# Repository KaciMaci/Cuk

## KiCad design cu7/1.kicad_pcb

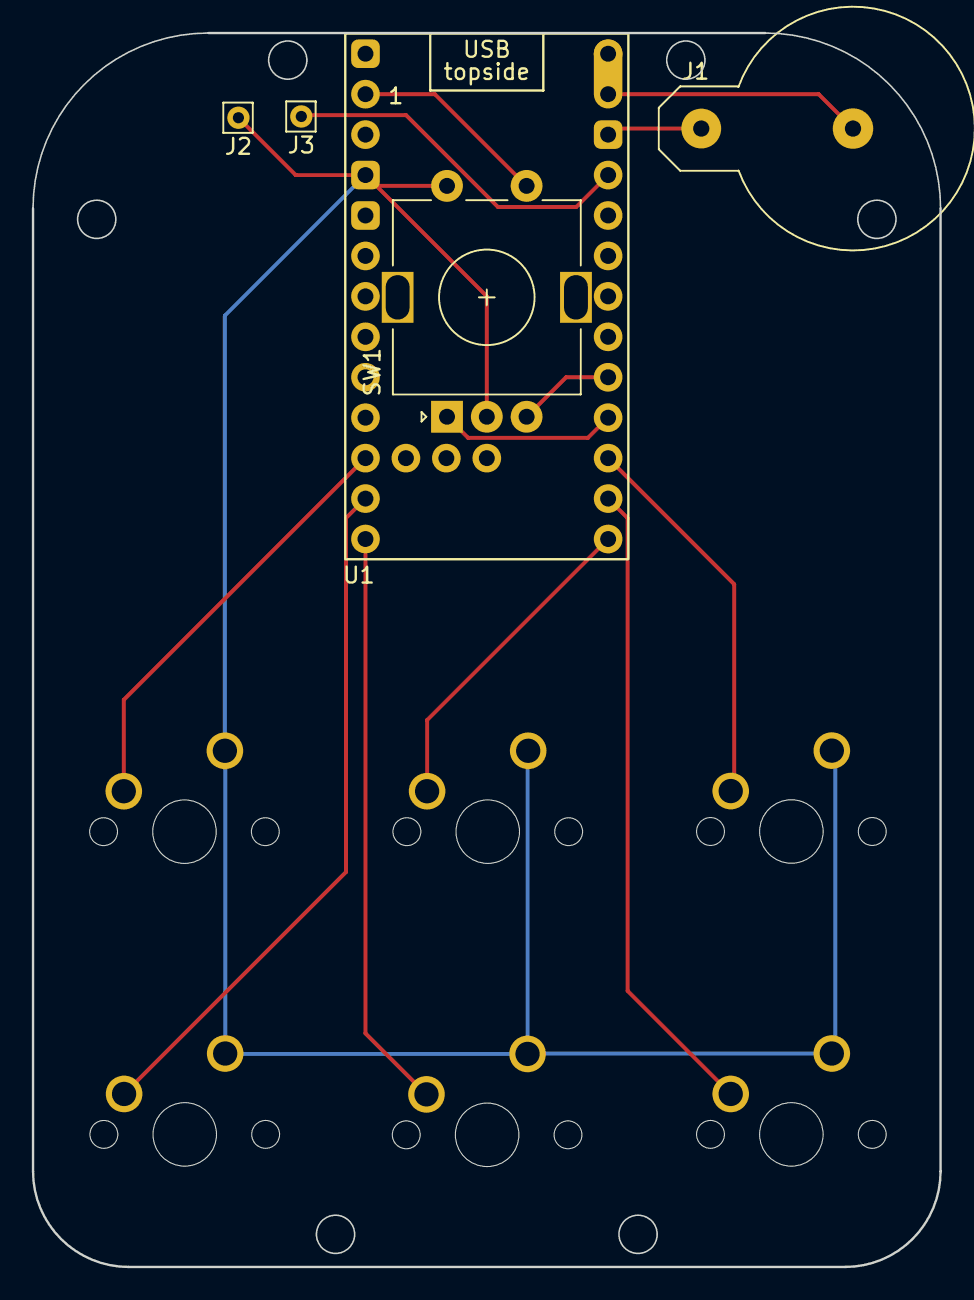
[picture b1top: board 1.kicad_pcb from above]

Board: 2 copper layers, 57.0 x 77.5 mm, 11 parts (0 on the bottom side), 12 nets.

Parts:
J1: Conn_01x02; BatteryHolder_Keystone_500
J2, J3: Conn_01x01; Pin_D0.7mm_L6.5mm_W1.8mm_FlatFork
MX1, MX2, MX3, MX4, MX5, MX6: MX_SW_solder; SW_MX_1u
SW1: RotaryEncoder_Switch; RotaryEncoder_Alps_EC11E-Switch_Vertical_H20mm
U1: nice_nano; nice_nano_AH_Reversible

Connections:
unnamed: J1.1, J2.1, MX1.2, MX2.2, MX3.2, MX4.2, MX5.2, MX6.2, SW1.C, SW1.S2, U1.3 (GND), U1.14 (GND)
unnamed: J1.2, U1.13 (BAT+), U1.29 (BAT+)
unnamed: J3.1, U1.15 (RST)
unnamed: MX6.1, U1.23 (P0-10-LF)
unnamed: SW1.S1, U1.1 (P0.06)
unnamed: MX2.1, U1.24 (P0.09-LF)
unnamed: MX1.1, U1.10 (P0.11)
unnamed: MX4.1, U1.11 (P1.04-LF)
unnamed: MX5.1, U1.12 (P1.06-LF)
unnamed: MX3.1, U1.22 (P1.11-LF)
unnamed: SW1.A, U1.21 (P1.13-LF)
unnamed: SW1.B, U1.20 (P1.15-LF)

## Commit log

2023-07-14 Initial User Config.
2023-07-14 compile
2023-08-16 Rename Kconfig.deconfig to Kconfig.defconfig
